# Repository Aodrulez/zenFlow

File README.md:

# ZenFlow
## My endgame 18 key custom keyboard 

Kailh Choc V1 variant:

MX 3d printed + hand wired variant:

ZenFlow is a fully custom split wireless keyboard made using Ergogen + KiCad. It's powered by [ZMK](https://zmk.dev/). Check [keymap](./keymap) for more details. 
## Features

- 18 keys
- Split, ortholinear
- Fully wireless, compatible with ZMK
- Supports both hot-swap as well as direct soldering of Kailh Choc v1 switches
- Supports nice!view displays
- Reversible PCB
- Mounting holes for a case

Note (Kailh Choc V1 variant): `Solder all the reversible pads & components (except battery, power switch & reset button) on the bottom side of each half as instructed on the PCB` 

## Requirements (Kailh Choc V1 variant)
| Part | Specification |
| ------ | ------ |
| MCU | 2x nice!nano or SuperMini |
| Battery | 2x Lipo battery (301230)|
| Power switch | 2x MSK-12C02 or compatible |
| Reset button | 2x B3U-1000P(M) |
| Switches | 18x Kailh Choc v1 |
| Keycaps | 16x Kailh Choc v1 1u & 2x Kailh Choc v1 2u |
| Hotswap sockets (Optional) | 18x Kailh Choc v1 |
| Display (Optional) | 2x nice!view |

## Credits
- Ben Vallack for the videos & his Piano keyboard for inspiration
- [Ergogen](https://docs.ergogen.xyz/) which was used for most of the designing & FlatFootFox for the tutorial series 
- [ZMK](https://zmk.dev/) community in general

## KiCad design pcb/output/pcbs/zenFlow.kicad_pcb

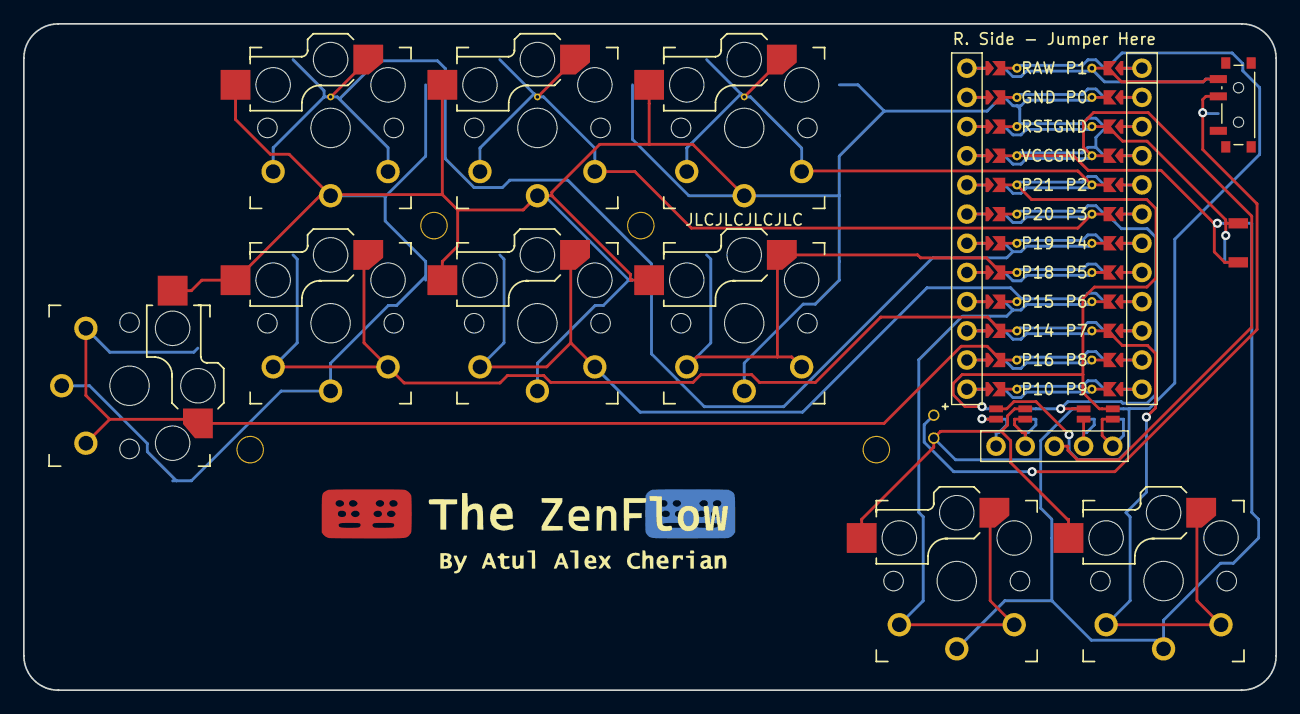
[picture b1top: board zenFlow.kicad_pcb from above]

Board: 2 copper layers, 109.0 x 58.0 mm, 21 parts (0 on the bottom side), 21 nets.

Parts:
BAT: bat
DISP1: nice!view
H1, H2, H3, H4: mounting_hole
MCU1: nice_nano
S1, S2, S3, S4, S5, S6, S7, S8, S9: PG1350
S10: SW_SPST_B3U-1000P
SW1: power_switch
Via1, Via2, Via3: VIA-0.6mm

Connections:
BAT_P: BAT.2, SW1.2, SW1.5
DISP1_1: DISP1.1, DISP1.10, DISP1.23
DISP1_2: DISP1.2, DISP1.11, DISP1.22
DISP1_4: DISP1.4, DISP1.12, DISP1.21
DISP1_5: DISP1.5, DISP1.13, DISP1.20
GND: BAT.1, DISP1.15, DISP1.25, MCU1.2, MCU1.121, MCU1.122, S1.2, S2.2, S3.2, S4.2, S5.2, S6.2, S7.2, S8.2, S9.2, S10.2
P1: DISP1.14, DISP1.24, MCU1.124
P2: DISP1.17, DISP1.27, MCU1.120
P3: DISP1.16, DISP1.26, MCU1.119
P5: MCU1.117, S6.1
P6: MCU1.116, S4.1
P7: MCU1.115, S2.1
P8: MCU1.114, S1.1
P14: MCU1.10, S9.1
P15: MCU1.9, S8.1
P19: MCU1.7, S3.1, Via1.1
P20: MCU1.6, S5.1, Via2.1
P21: MCU1.5, S7.1, Via3.1
RAW: MCU1.1, SW1.3, SW1.6
RST: MCU1.3, S10.1
VCC: DISP1.3, MCU1.4

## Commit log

2024-01-30 Rename zenSplit.keymap to zenFlow.keymap
2024-02-17 Update zenFlow.keymap
    update to 3.5 Zephyr branch
2024-06-25 Create LICENSE
